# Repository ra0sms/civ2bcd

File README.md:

## Converter Icom CI-V to Yaesu BCD band data

PCB dimensions: 70*45 mm

Power supply: 7-15VDC (20mA)

Baud rate: 9600 kb/s

2 separated Yaesu BCD outputs

1 Icom CI-V output

More information - https://ra0sms.com/civ2bcd

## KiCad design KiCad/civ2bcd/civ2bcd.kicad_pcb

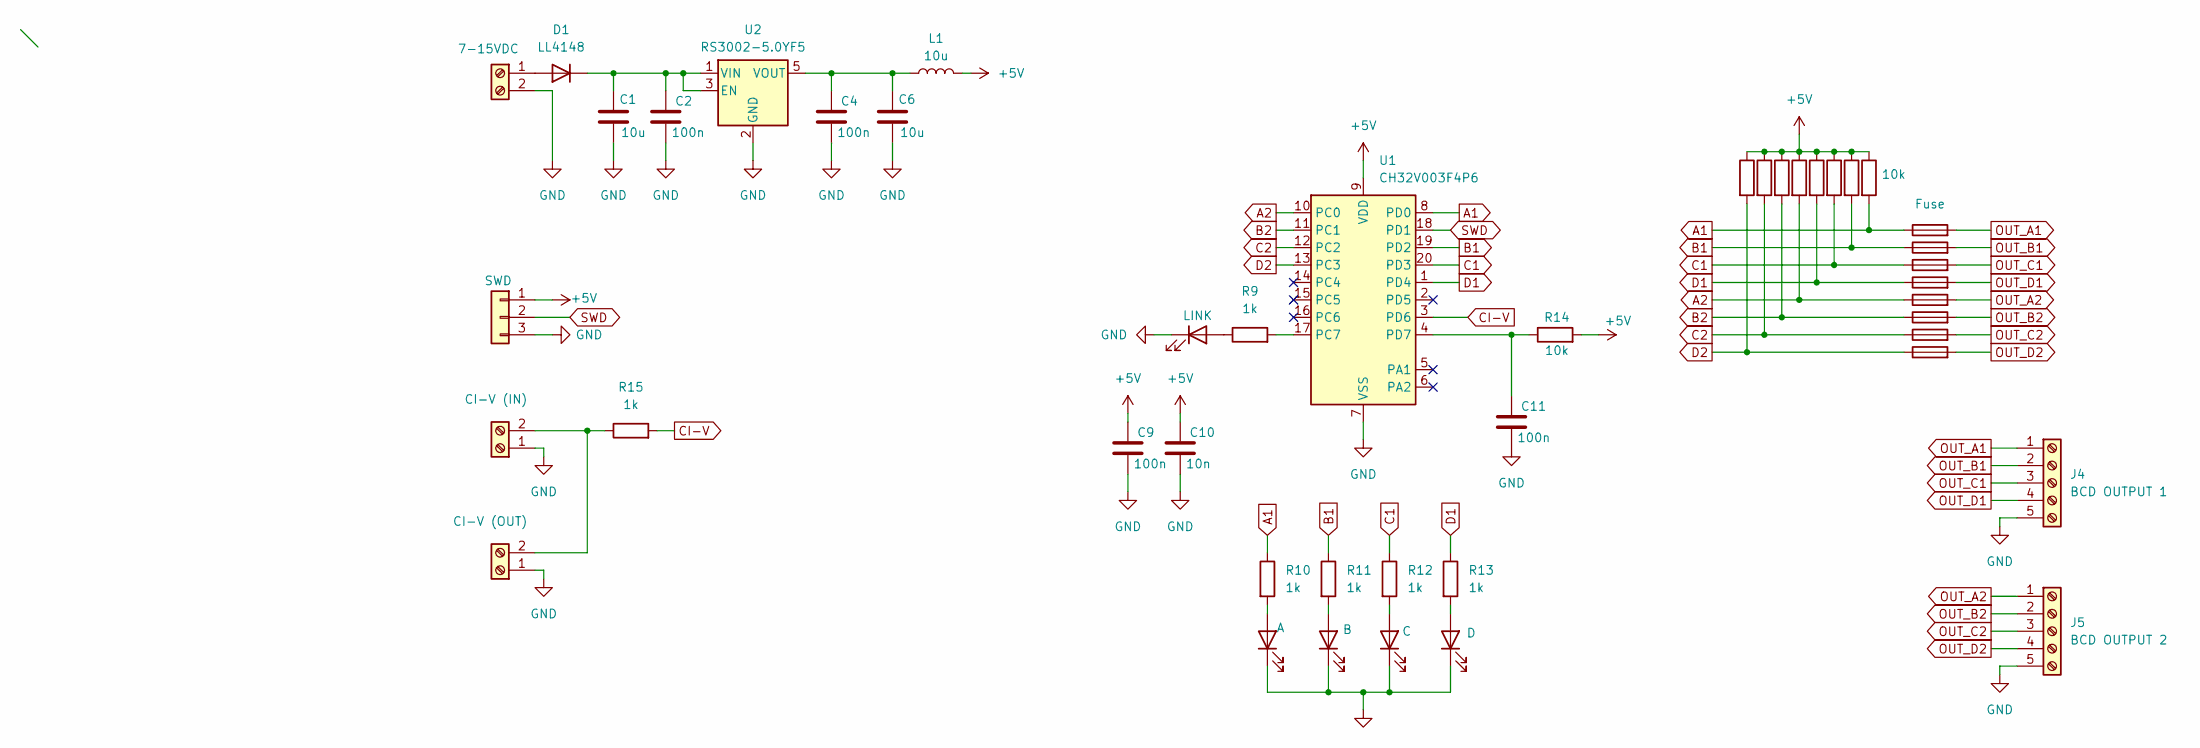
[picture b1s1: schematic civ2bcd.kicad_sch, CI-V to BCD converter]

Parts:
C1, C6: 10u; C_1206_3216Metric_Pad1.33x1.80mm_HandSolder
C2, C4, C9, C11: 100n; C_1206_3216Metric_Pad1.33x1.80mm_HandSolder
C10: 10n; C_1206_3216Metric_Pad1.33x1.80mm_HandSolder
D1: LL4148; D_MiniMELF
D2: LINK; LED_1206_3216Metric
D3: A; LED_1206_3216Metric
D4: B; LED_1206_3216Metric
D5: C; LED_1206_3216Metric
D6: D; LED_1206_3216Metric
F1, F2, F3, F4, F5, F6, F7, F8: Fuse; R_1206_3216Metric
J1: 7-15VDC; TerminalBlock_MetzConnect_Type055_RT01502HDWU_1x02_P5.00mm_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
J2: CI-V (OUT); TerminalBlock_MetzConnect_Type055_RT01502HDWU_1x02_P5.00mm_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
J3: SWD; PinSocket_1x03_P2.54mm_Vertical
J4: BCD OUTPUT 1; TerminalBlock_MetzConnect_Type011_RT05505HBLC_1x05_P5.00mm_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
J5: BCD OUTPUT 2; TerminalBlock_MetzConnect_Type011_RT05505HBLC_1x05_P5.00mm_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
J6: CI-V (IN); TerminalBlock_MetzConnect_Type055_RT01502HDWU_1x02_P5.00mm_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
L1: 10u; L_1206_3216Metric
R5, R6, R7, R8, R14, R19, R20, R21, R22: 10k; R_1206_3216Metric
R9, R10, R11, R12, R13, R15: 1k; R_1206_3216Metric
U1: CH32V003F4P6; TSSOP-20_4.4x6.5mm_P0.65mm
U2: RS3002-5.0YF5; SOT-23-5

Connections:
+5V: C9.1, C10.1, J3.1, L1.2, R5.1, R6.1, R7.1, R8.1, R14.2, R19.1, R20.1, R21.1, R22.1, U1.9 (VDD)
A1: F1.1, R5.2, R10.1, U1.8 (PD0)
A2: F5.1, R19.2, U1.10 (PC0)
B1: F2.1, R6.2, R11.1, U1.19 (PD2)
B2: F6.1, R20.2, U1.11 (PC1)
C1: F3.1, R7.2, R12.1, U1.20 (PD3)
C2: F7.1, R21.2, U1.12 (PC2)
CI-V: R15.2, U1.3 (PD6)
D1: F4.1, R8.2, R13.1, U1.1 (PD4)
D2: F8.1, R22.2, U1.13 (PC3)
GND: C1.2, C2.2, C4.2, C6.2, C9.2, C10.2, C11.2, D2.1 (K), D3.1 (K), D4.1 (K), D5.1 (K), D6.1 (K), J1.2, J2.1, J3.3, J4.5, J5.5, J6.1, U1.7 (VSS), U2.2 (GND)
unnamed: D1.2 (A), J1.1
unnamed: C1.1, C2.1, D1.1 (K), U2.1 (VIN), U2.3 (EN)
unnamed: D2.2 (A), R9.1
unnamed: D3.2 (A), R10.2
unnamed: D4.2 (A), R11.2
unnamed: D5.2 (A), R12.2
unnamed: D6.2 (A), R13.2
unnamed: J2.2, J6.2, R15.1
unnamed: R9.2, U1.17 (PC7)
unnamed: C11.1, R14.1, U1.4 (PD7)
unnamed: C4.1, C6.1, L1.1, U2.5 (VOUT)
OUT_A1: F1.2, J4.1
OUT_A2: F5.2, J5.1
OUT_B1: F2.2, J4.2
OUT_B2: F6.2, J5.2
OUT_C1: F3.2, J4.3
OUT_C2: F7.2, J5.3
OUT_D1: F4.2, J4.4
OUT_D2: F8.2, J5.4
SWD: J3.2, U1.18 (PD1)

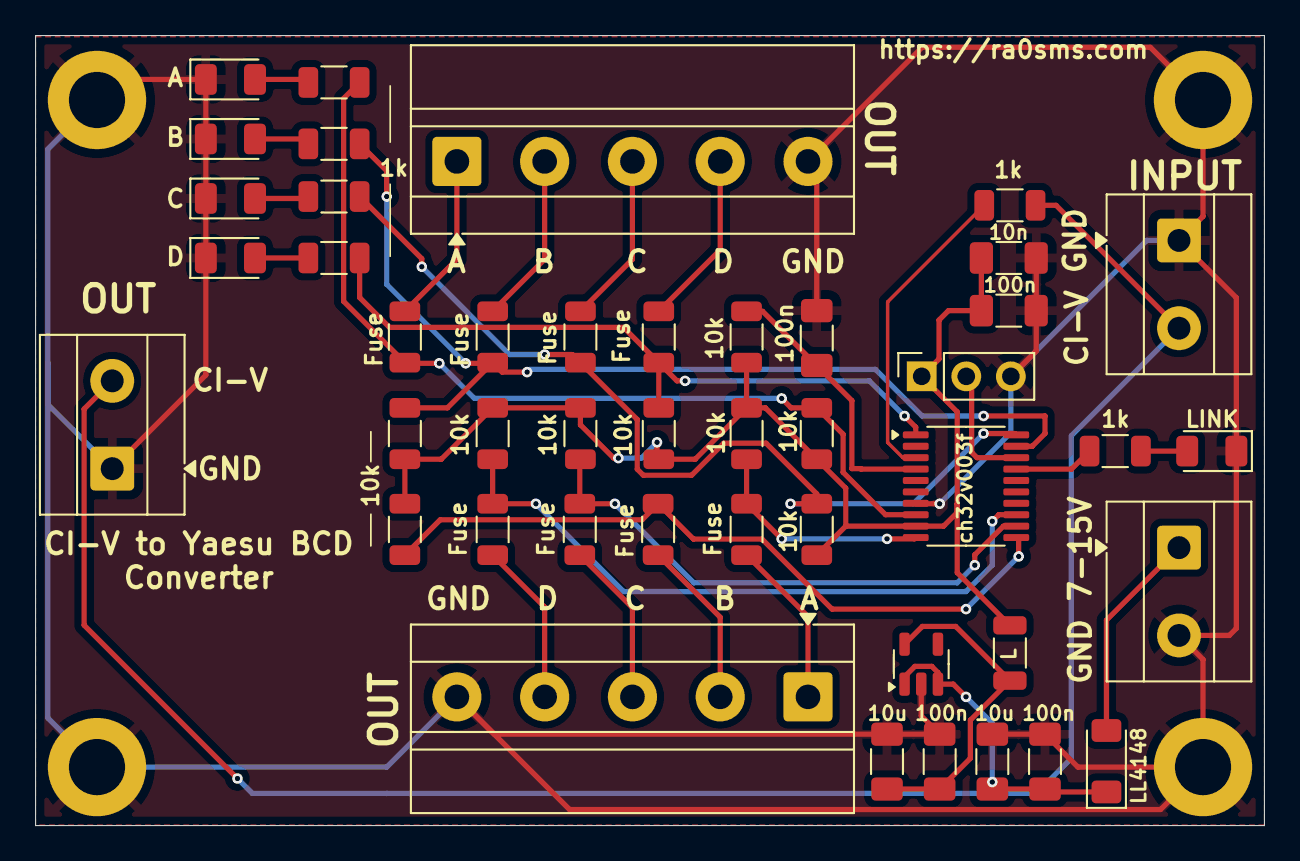
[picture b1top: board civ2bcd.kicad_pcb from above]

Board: 2 copper layers, 70.0 x 45.0 mm, 45 parts (0 on the bottom side), 31 nets.

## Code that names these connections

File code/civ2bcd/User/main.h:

#include "debug.h"

#define BAUD_RATE 9600

#define LED_Pin GPIO_Pin_7
#define LED_GPIO_Port GPIOC
//**************
#define OUT_A1 GPIO_Pin_0
#define OUT_A1_Port GPIOD
//***************
#define OUT_B1 GPIO_Pin_2
#define OUT_B1_Port GPIOD
//***************
#define OUT_C1 GPIO_Pin_3
#define OUT_C1_Port GPIOD
//***************
#define OUT_D1 GPIO_Pin_4
#define OUT_D1_Port GPIOD
//**************
#define OUT_A2 GPIO_Pin_0
#define OUT_A2_Port GPIOC
//***************
#define OUT_B2 GPIO_Pin_1
#define OUT_B2_Port GPIOC
//***************
#define OUT_C2 GPIO_Pin_2
#define OUT_C2_Port GPIOC
//***************
#define OUT_D2 GPIO_Pin_3
#define OUT_D2_Port GPIOC
//**************

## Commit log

2025-06-19 add readme and pics
2025-12-15 fix issues with civ input
2026-01-14 fix civ connection
